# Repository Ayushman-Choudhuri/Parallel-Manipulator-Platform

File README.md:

# Circle - A Robotic Parallel-Manipulator-Platform

## 1.  Project Description

Circle is an open source 6 DOF robotic parallel manipulator platform. This project was started with the aim of building a stabilization platform for critical payloads like cameras in both linear as well as rotational axes. Additional features will be added as the project matures.   

Project link on my website: https://www.ayushmanchoudhuri.com/circle

## 2. Software

### 2.1 Software Packages Used

#### 2.1.1 Software Development
1. STM32CubeIDE - V1.2.0
2. STM32CubeMX - V6.2.0
3. STM-STUDIO-STM32 - V3.6.0
4. Jupyter Notebook 6.0.1

#### 2.1.2 Hardware Development
1. Solidworks 2018
2. Ultimaker Cura 3.4.1
3. Eagle 9.6.2

### 2.2 Setup

#### 2.2.1 STM Environment

- The Circle_Software.ioc (Software > Circle_Software.ioc) file can be imported into the STM32CubeMX environment and then the pin settings of the STM32F103C8T6 microcontroller can be viewed and modified 
- The .cproject file (Software > .cproject) can be used to import the project into the STM32CUBE IDE Environment.
- Core (Software > Core) contains all the source (Src) and the header files (inc) needed. 
- Variable Viewer (Software>Variable Viewer) contains the .tsc and .tsp files needed to view variables using STM STUDIO

#### 2.2.2 Python - IK Analysis

- The inverse kinematics analysis of the robot can be found in the  "Inverse Kinematics Solver - Python" Folder. The file can be imported into a jupyter notebook and analysed

## 3. Hardware

### 3.1 Controller

The controller is a double sided PCB with the following components mounted on it:
  - DRV8825 Stepper Motor Driver Module
  - STM32F103C8T6 Microcontroller based development board (Blue Pill). The core is an ARM CORTEX M3
  - Mini 360 Step Down Buck Converter Power Module
  - USB to UART TTL 5V 3.3V FT232RL 
  - 3 way DIP switch (To set microstepping mode of the stepper motor drivers)
  - Input port for a MPU 9250 sensor which can be attatched to the end effector for pose feedback
 
 The controller is powered using a 12V 10A SMPS power module

### 3.2 Actuation

The Actuation of the robot links are done using six NEMA 17 4.4 Kgcm motors.

### 3.3 Robot Structure and Links

The robot has a 6 RSS structure. The CAD models can be found in the file - CAD MODELS

### 3.4 Manufacturing

- All the structural support items and end effectors can be 3D printed
- If a 3D printer cannot print the base plates of the robot, they can also be made out of Acrylic sheets (min 5mm) using laser cutting methods
- The S-S links can be made by joining two femals M6 spherical joint bearings using a M6 threaded rod. 

## 4. Future Work
- Closed loop implementation and stablization using MPU 9250 sensor feedback
- Replacement of SMPS with Lithium Polymer Battery
- ROS Implementation 
- Replacing the STM 32 microcontroller with a Raspberry Pi 4

## 5. Contributing

Pull requests are welcome. For major changes, please open an issue first to discuss what you would like to change.

## 6. License

MIT

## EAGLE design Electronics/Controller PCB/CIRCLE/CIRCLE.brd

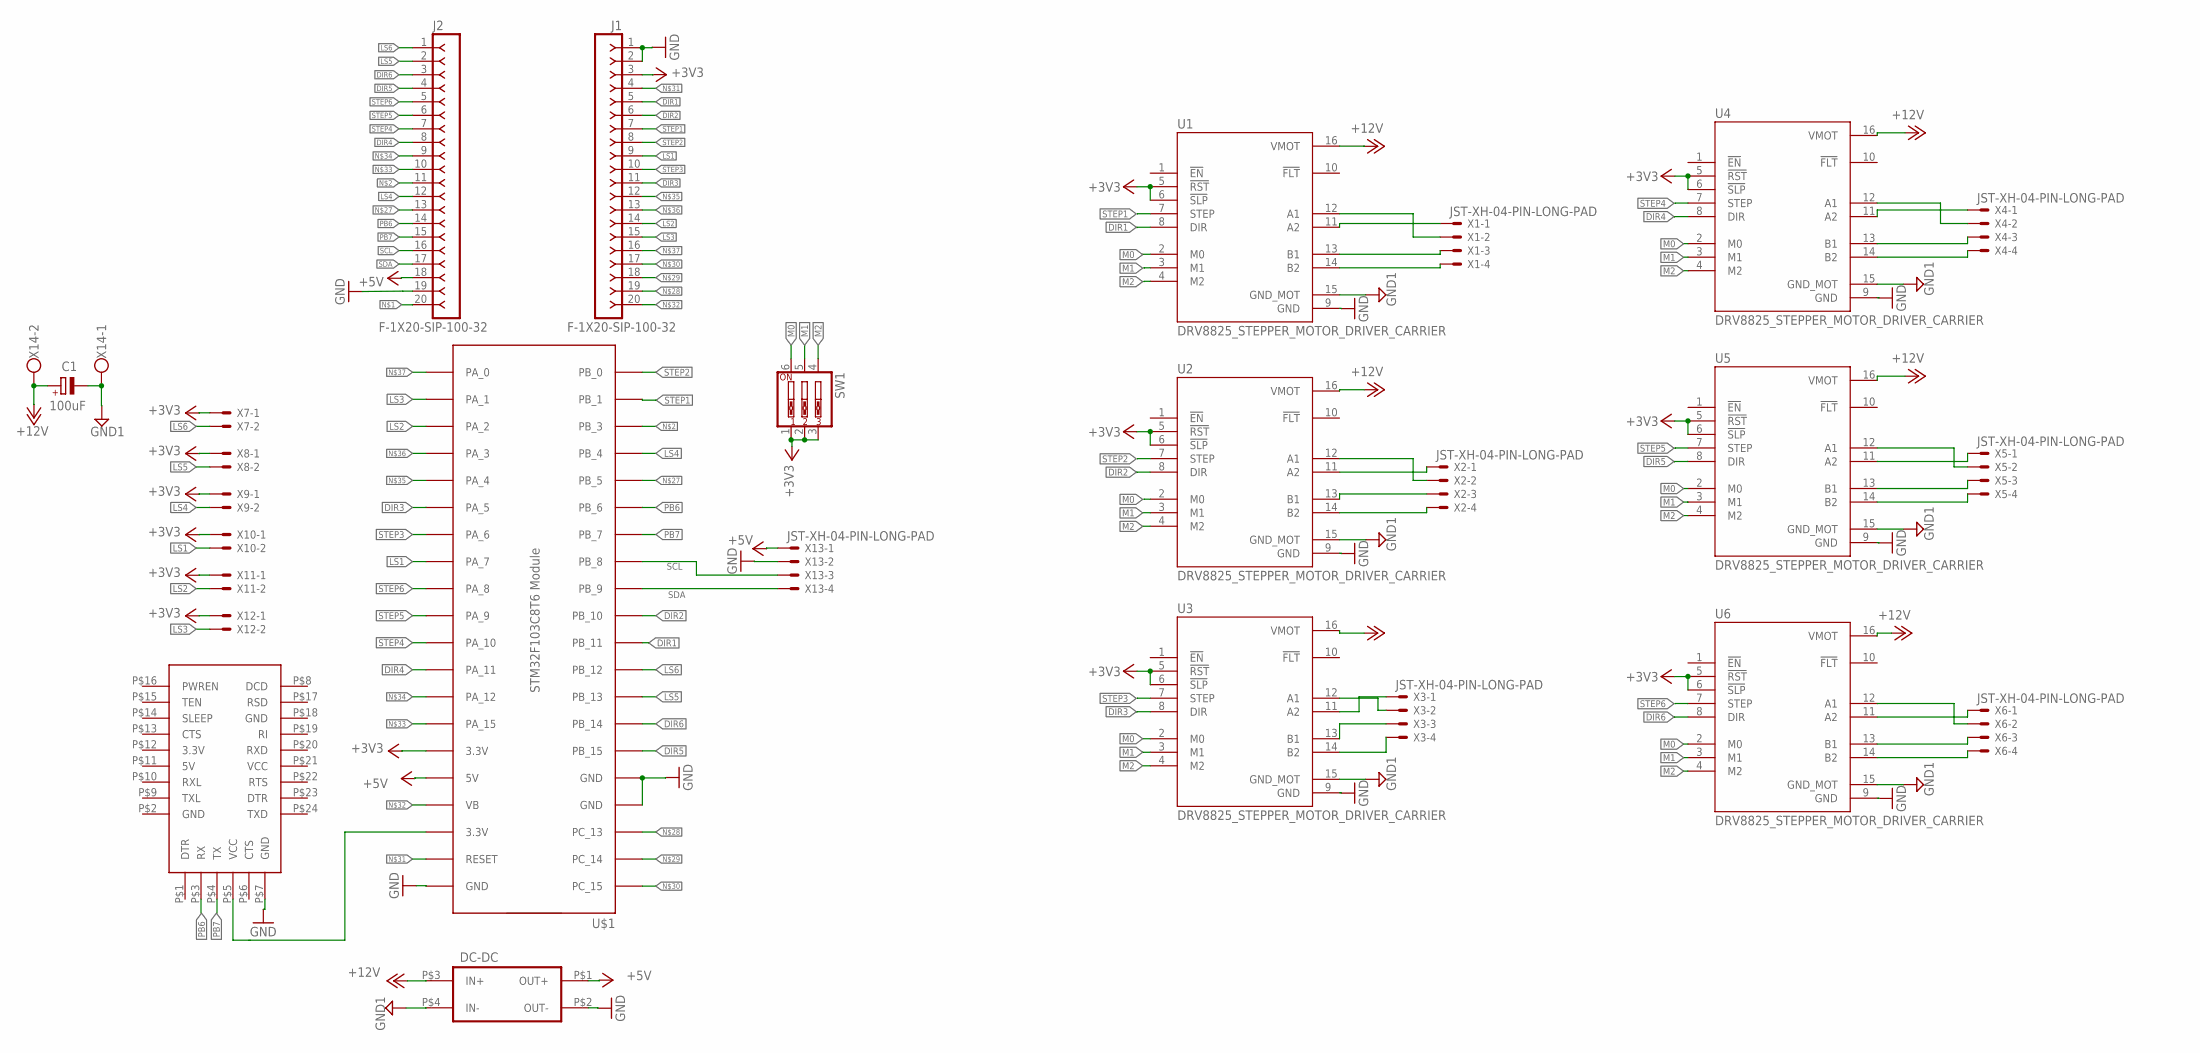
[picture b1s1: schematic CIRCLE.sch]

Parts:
C1: 100uF; E3,5-8
J1, J2: F-1X20-SIP-100-32; SIP-100-20-32
SW1: SW_DIP-3; EDG-03
U1, U2, U3, U4, U5, U6: DRV8825_STEPPER_MOTOR_DRIVER_CARRIER; IC_DRV8825_STEPPER_MOTOR_DRIVER_CARRIER
U$1: STM32F103C8T6-MODULE
U$2: DC-DC_CONV
U$3: FT232RL_FTDI
X1, X2, X3, X4, X5, X6, X13: JST-XH-04-PIN-LONG-PAD; JST-XH-04-PACKAGE-LONG-PAD
X7, X8, X9, X10, X11, X12: JST-XH-02-PIN-LONG-PAD; JST-XH-02-PACKAGE-LONG-PAD
X14: W237-102

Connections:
+3V3: J1.3, SW1.1, SW1.2, SW1.3, U1.5 (!RST), U1.6 (!SLP), U2.5 (!RST), U2.6 (!SLP), U3.5 (!RST), U3.6 (!SLP), U4.5 (!RST), U4.6 (!SLP), U5.5 (!RST), U5.6 (!SLP), U6.5 (!RST), U6.6 (!SLP), U$1.3.3V@2 (3.3V), X7.1, X8.1, X9.1, X10.1, X11.1, X12.1
+5V: J2.18, U$1.5V, U$2.P$1 (OUT+), X13.1
+12V: C1.+, U1.16 (VMOT), U2.16 (VMOT), U3.16 (VMOT), U4.16 (VMOT), U5.16 (VMOT), U6.16 (VMOT), U$2.P$3 (IN+), X14.2
DIR1: J1.5, U1.8 (DIR), U$1.PB_11
DIR2: J1.6, U2.8 (DIR), U$1.PB_10
DIR3: J1.11, U3.8 (DIR), U$1.PA_5
DIR4: J2.8, U4.8 (DIR), U$1.PA_11
DIR5: J2.4, U5.8 (DIR), U$1.PB_15
DIR6: J2.3, U6.8 (DIR), U$1.PB_14
GND: J1.1, J1.2, J2.19, U1.9 (GND), U2.9 (GND), U3.9 (GND), U4.9 (GND), U5.9 (GND), U6.9 (GND), U$1.GND@1 (GND), U$1.GND@2 (GND), U$1.GND@3 (GND), U$2.P$2 (OUT-), U$3.P$7 (GND), X13.2
GND1: C1.-, U1.15 (GND_MOT), U2.15 (GND_MOT), U3.15 (GND_MOT), U4.15 (GND_MOT), U5.15 (GND_MOT), U6.15 (GND_MOT), U$2.P$4 (IN-), X14.1
LS1: J1.9, U$1.PA_7, X10.2
LS2: J1.14, U$1.PA_2, X11.2
LS3: J1.15, U$1.PA_1, X12.2
LS4: J2.12, U$1.PB_4, X9.2
LS5: J2.2, U$1.PB_13, X8.2
LS6: J2.1, U$1.PB_12, X7.2
M0: SW1.6, U1.2 (M0), U2.2 (M0), U3.2 (M0), U4.2 (M0), U5.2 (M0), U6.2 (M0)
M1: SW1.5, U1.3 (M1), U2.3 (M1), U3.3 (M1), U4.3 (M1), U5.3 (M1), U6.3 (M1)
M2: SW1.4, U1.4 (M2), U2.4 (M2), U3.4 (M2), U4.4 (M2), U5.4 (M2), U6.4 (M2)
unnamed: J2.20, U$1.3.3V@1 (3.3V), U$3.P$5 (VCC)
unnamed: J2.11, U$1.PB_3
unnamed: U1.14 (B2), X1.4
unnamed: U1.13 (B1), X1.3
unnamed: U1.12 (A1), X1.2
unnamed: U1.11 (A2), X1.1
unnamed: U2.14 (B2), X2.4
unnamed: U2.13 (B1), X2.3
unnamed: U2.11 (A2), X2.1
unnamed: U2.12 (A1), X2.2
unnamed: U4.14 (B2), X4.4
unnamed: U4.13 (B1), X4.3
unnamed: U4.11 (A2), X4.1
unnamed: U4.12 (A1), X4.2
unnamed: U5.14 (B2), X5.4
unnamed: U5.13 (B1), X5.3
unnamed: U5.11 (A2), X5.1
unnamed: U5.12 (A1), X5.2
unnamed: U6.14 (B2), X6.4
unnamed: U6.13 (B1), X6.3
unnamed: U6.11 (A2), X6.1
unnamed: U6.12 (A1), X6.2
unnamed: U3.14 (B2), X3.4
unnamed: U3.13 (B1), X3.3
unnamed: U3.11 (A2), X3.1
unnamed: U3.12 (A1), X3.2
unnamed: J2.13, U$1.PB_5
unnamed: J1.19, U$1.PC_13
unnamed: J1.18, U$1.PC_14
unnamed: J1.17, U$1.PC_15
unnamed: J1.4, U$1.RESET
unnamed: J1.20, U$1.VB
unnamed: J2.10, U$1.PA_15
unnamed: J2.9, U$1.PA_12
unnamed: J1.12, U$1.PA_4
unnamed: J1.13, U$1.PA_3
unnamed: J1.16, U$1.PA_0
PB6: J2.14, U$1.PB_6, U$3.P$3 (RX)
PB7: J2.15, U$1.PB_7, U$3.P$4 (TX)
SCL: J2.16, U$1.PB_8, X13.3
SDA: J2.17, U$1.PB_9, X13.4
STEP1: J1.7, U1.7 (STEP), U$1.PB_1
STEP2: J1.8, U2.7 (STEP), U$1.PB_0
STEP3: J1.10, U3.7 (STEP), U$1.PA_6
STEP4: J2.7, U4.7 (STEP), U$1.PA_10
STEP5: J2.6, U5.7 (STEP), U$1.PA_9
STEP6: J2.5, U6.7 (STEP), U$1.PA_8

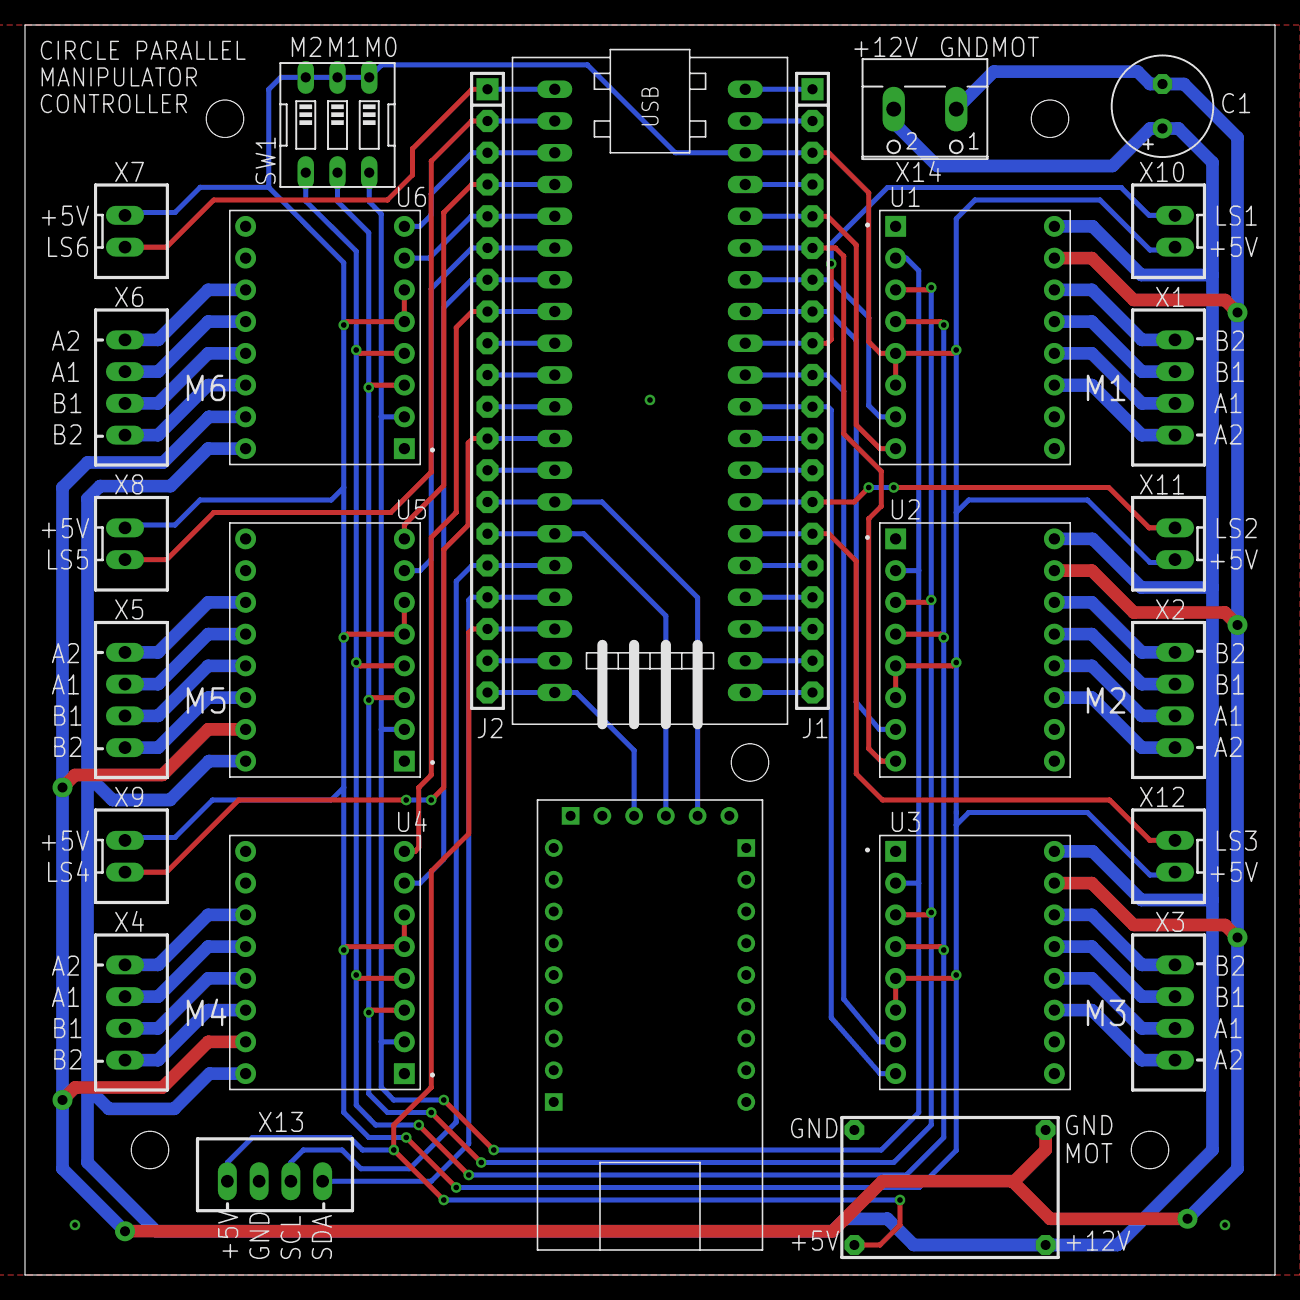
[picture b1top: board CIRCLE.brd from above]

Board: 2 copper layers, 100.0 x 100.0 mm, 27 parts (0 on the bottom side), 67 nets.

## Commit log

2021-05-28 Proposed sections
2021-05-28 Initial License Commit
2021-05-29 MIT License
2021-05-29 Updated Descriptions
    1. Updated project description
    2. Updated version numbering rules
    3. Updated Contributing field description
    4. Updated license type
2021-05-29 New motor system initialization branch added
2021-05-29 TIM3 CH1 initialized to PWM Generation mode on a 10 KHz Frequency
2021-06-06 Motor Timers Initialized and Step Angle Testing for Motor 1
2021-07-21 Stable Limit Switch Detection Logic
2021-07-21 no message
2021-07-21 Updated Limit Switch Detection Logic
2021-07-22 Updated Motor Angle Function
2021-08-01 Updated MotorAngle Function
2021-08-03 Corrected Motor Actuation Function and updated hardware level motor control routine in Systick Loop.
2021-08-08 Updated Motor Angle Test function and resolved Motor 5 direction issue ( Motor 5 direction pin was set to PA15 and has now been changed to PB15 as per controller hardware circuit)
2021-08-08 Temporary fix to the issue of MotorCurrentStepCount variable of data type uint32_t overshooting below 0 when the angle is decreasing. A more elegant solution will be implemented later
2021-08-10 Variable viewer update
2021-08-10 language settings change ?
2021-10-02 1. Robot CAD model added 2. Controller PCB files added
2021-11-28 Inverse Kinematics Solver Updated
2021-12-12 Updated Jupyter Notebook File
2021-12-12 README update
    Software, Hardware, Future work section added

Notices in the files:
parts and their libraries:
con-headers-jp female: Copyright (C) 2008, Bob Starr
